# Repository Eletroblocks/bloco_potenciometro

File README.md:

# potenciometro
Controla a QUANTIDADE de energia transmitida para os blocos seguintes.

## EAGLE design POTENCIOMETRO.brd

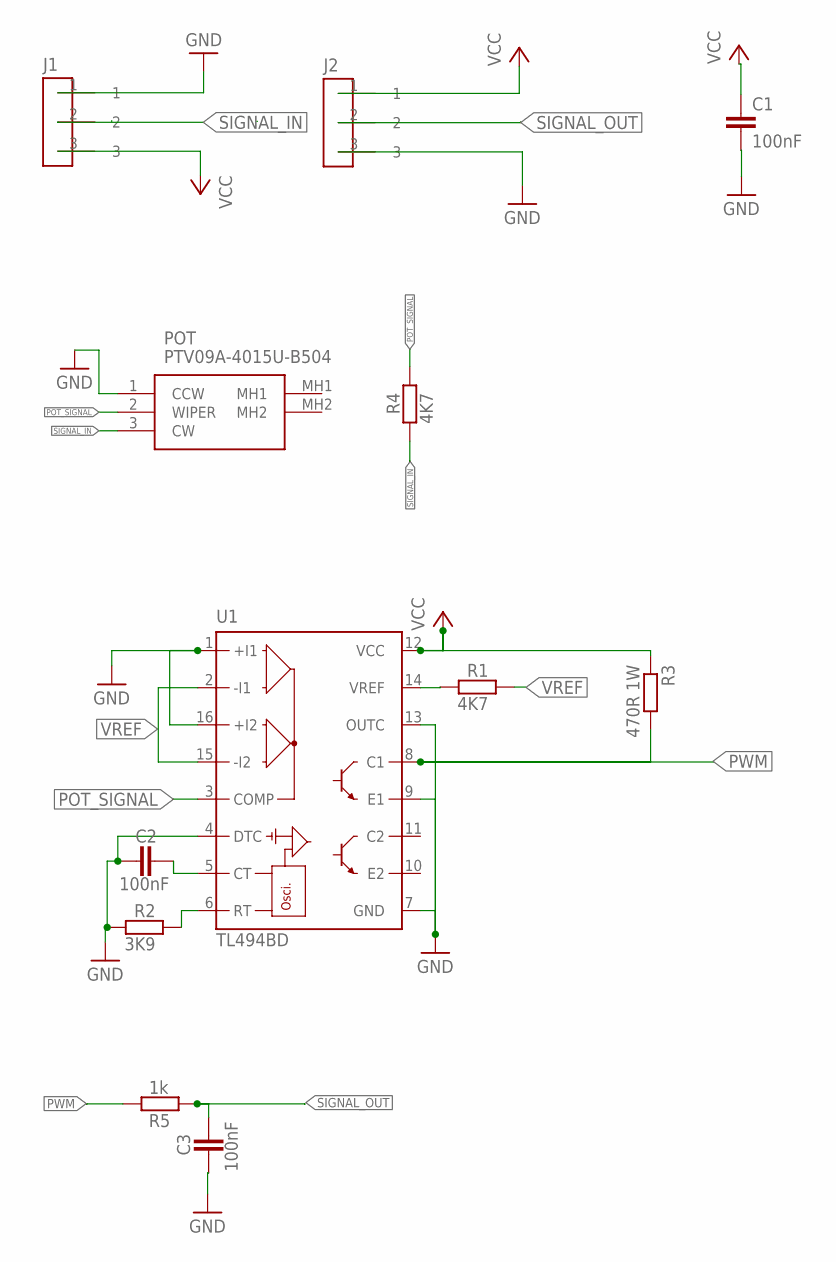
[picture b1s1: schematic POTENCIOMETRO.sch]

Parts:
C1, C2, C3: 100nF; C0805
J1: CONECTOR_MACHO; MALE
J2: CONECTOR_FEMEA; FEMALE
POT: PTV09A-4015U-B504; PTV09A4015UB104
R1, R4: 4K7; R0805W
R2: 3K9; R0805W
R3: 470R 1W; R2512
R5: 1k; R0805W
U1: TL494BD; SO16

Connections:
GND: C1.2, C2.1, C3.1, J1.1, J2.3, POT.1 (CCW), R2.2, U1.1 (+I1), U1.4 (DTC), U1.7 (GND), U1.9 (E1), U1.13 (OUTC), U1.16 (+I2)
unnamed: C2.2, U1.5 (CT)
unnamed: R1.2, U1.14 (VREF)
unnamed: R2.1, U1.6 (RT)
POT_SIGNAL: POT.2 (WIPER), R4.1, U1.3 (COMP)
PWM: R3.2, R5.1, U1.8 (C1)
SIGNAL_IN: J1.2, POT.3 (CW), R4.2
SIGNAL_OUT: C3.2, J2.2, R5.2
VCC: C1.1, J1.3, J2.1, R3.1, U1.12 (VCC)
VREF: R1.1, U1.2 (-I1), U1.15 (-I2)

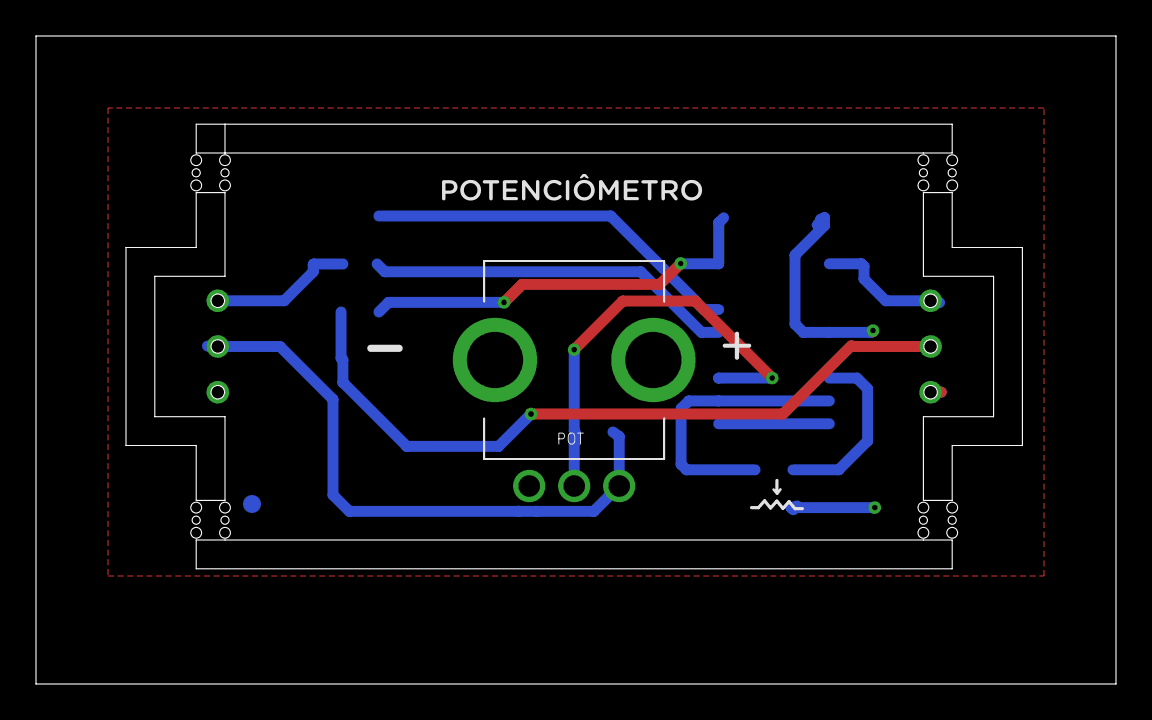
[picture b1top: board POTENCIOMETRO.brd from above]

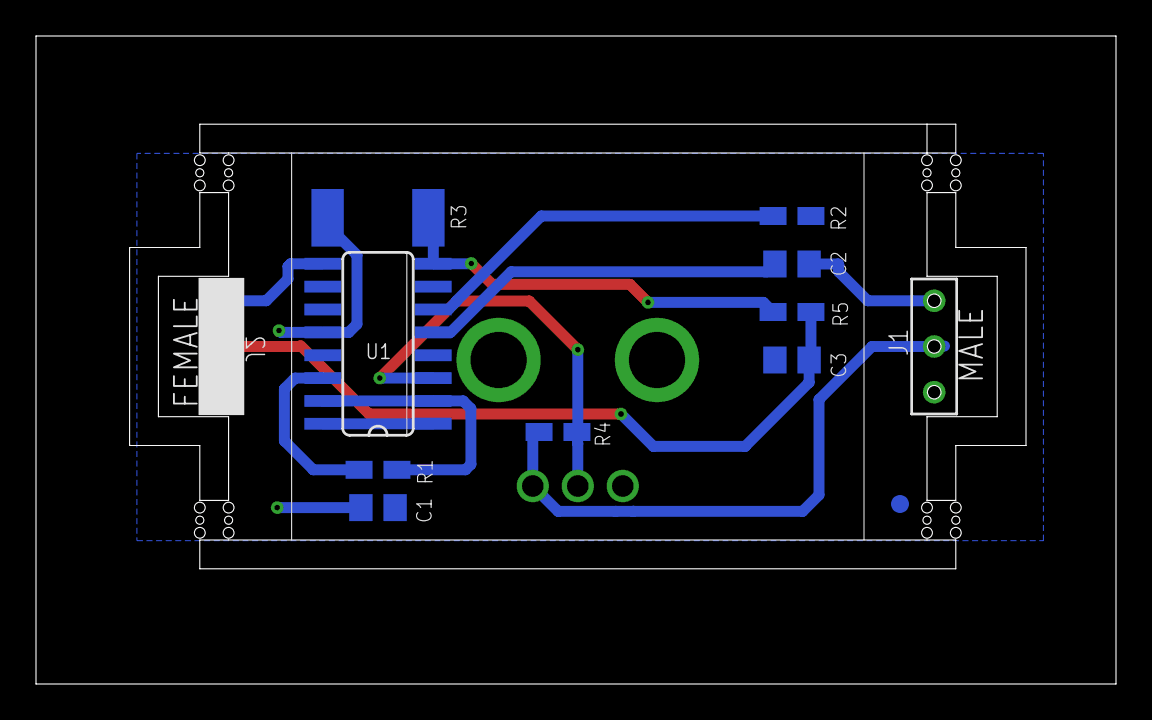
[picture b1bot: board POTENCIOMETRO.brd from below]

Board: 2 copper layers, 60.0 x 36.0 mm, 17 parts (10 on the bottom side), 10 nets.

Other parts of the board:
U$1: FIDUCIAL_G10
U$2, U$3, U$4, U$5: STAMP_DUPLO

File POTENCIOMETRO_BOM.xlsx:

BOM LIST POTENCIOMETRO
DESCRIPTION | QUANTITY | POSITION | PART NUMBER
RESISTOR 4K7 0805 | 2 | R1,R4 | CRCW08054K70FKEAC, can be replaced to similar
RESISTOR 3K9 0805 | 1 | R2 | CR0805-JW-392ELF, can be replaced to similar
RESISTOR 470R. 2512 | 1 | R3 | RC2512FK-07470RL , can be replaced to similar
CAPACITOR 100nF 0805 | 2 | C1,C2 | UMF212B7104KGHT, can be replaced to similar
POT10k PVT09A | 1 | POT | P090S-14T20BR10K
TL494 | 1 | U1 | TL494CNSRG4
MALE CONNECTOR | 1 | J1 | THIS COMPONENT IS PROVIDE BY ELETROBLOCKS
FEMALE CONNECTOR | 1 | J2 | THIS COMPONENT IS PROVIDE BY ELETROBLOCKS

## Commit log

2020-11-23 init project
2020-11-23 Create .gitignore
    aquivo para ignorar arquivos inúteis
2020-11-23 correção de pads, adição de label para versionamento, adição de resistor R4 para ajuste de sensibilidade e correção de entradas do POT
2020-11-23 correção de erro do duty clycle do PWM
2020-11-23 adição de filtro no SIGNAL_OUT para correção do Duty Clycle
2020-11-23 correção de label
2020-12-28 organizando arquivos
2020-12-28 imagem
2021-03-11 V1.1.1

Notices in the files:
parts and their libraries:
dicons: Copyright (C) 2004, Bob Starr (rtzaudio@mindspring.com)
